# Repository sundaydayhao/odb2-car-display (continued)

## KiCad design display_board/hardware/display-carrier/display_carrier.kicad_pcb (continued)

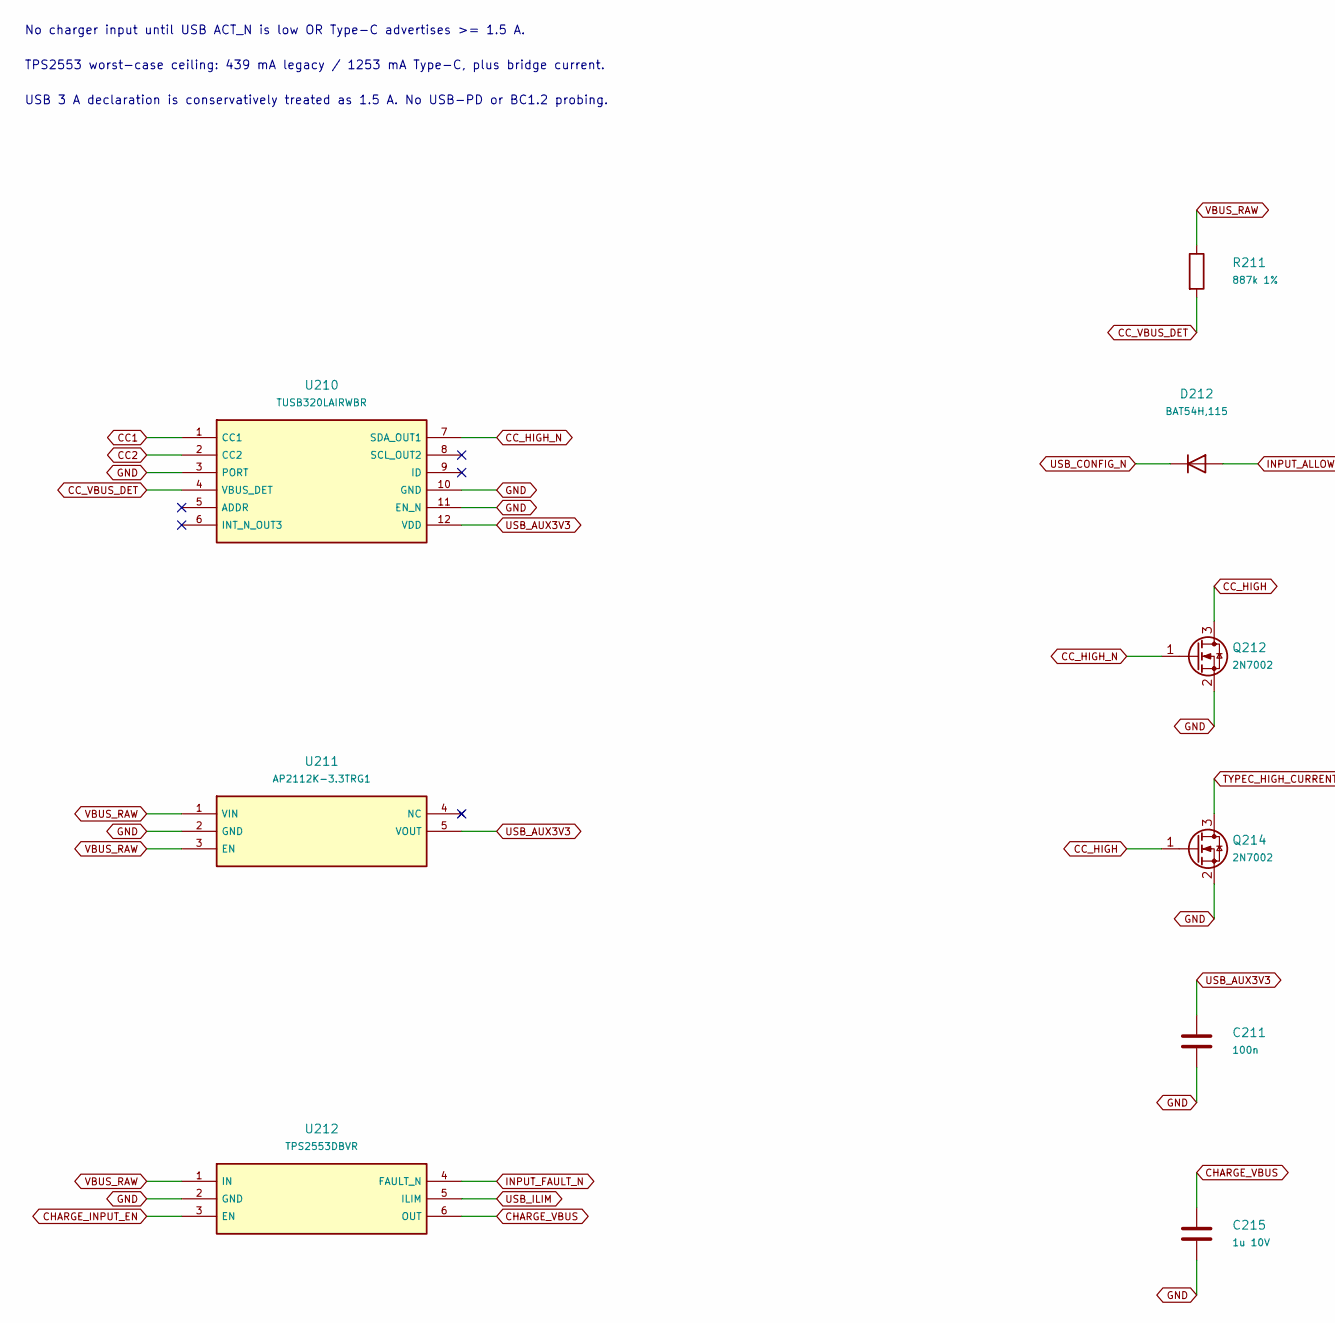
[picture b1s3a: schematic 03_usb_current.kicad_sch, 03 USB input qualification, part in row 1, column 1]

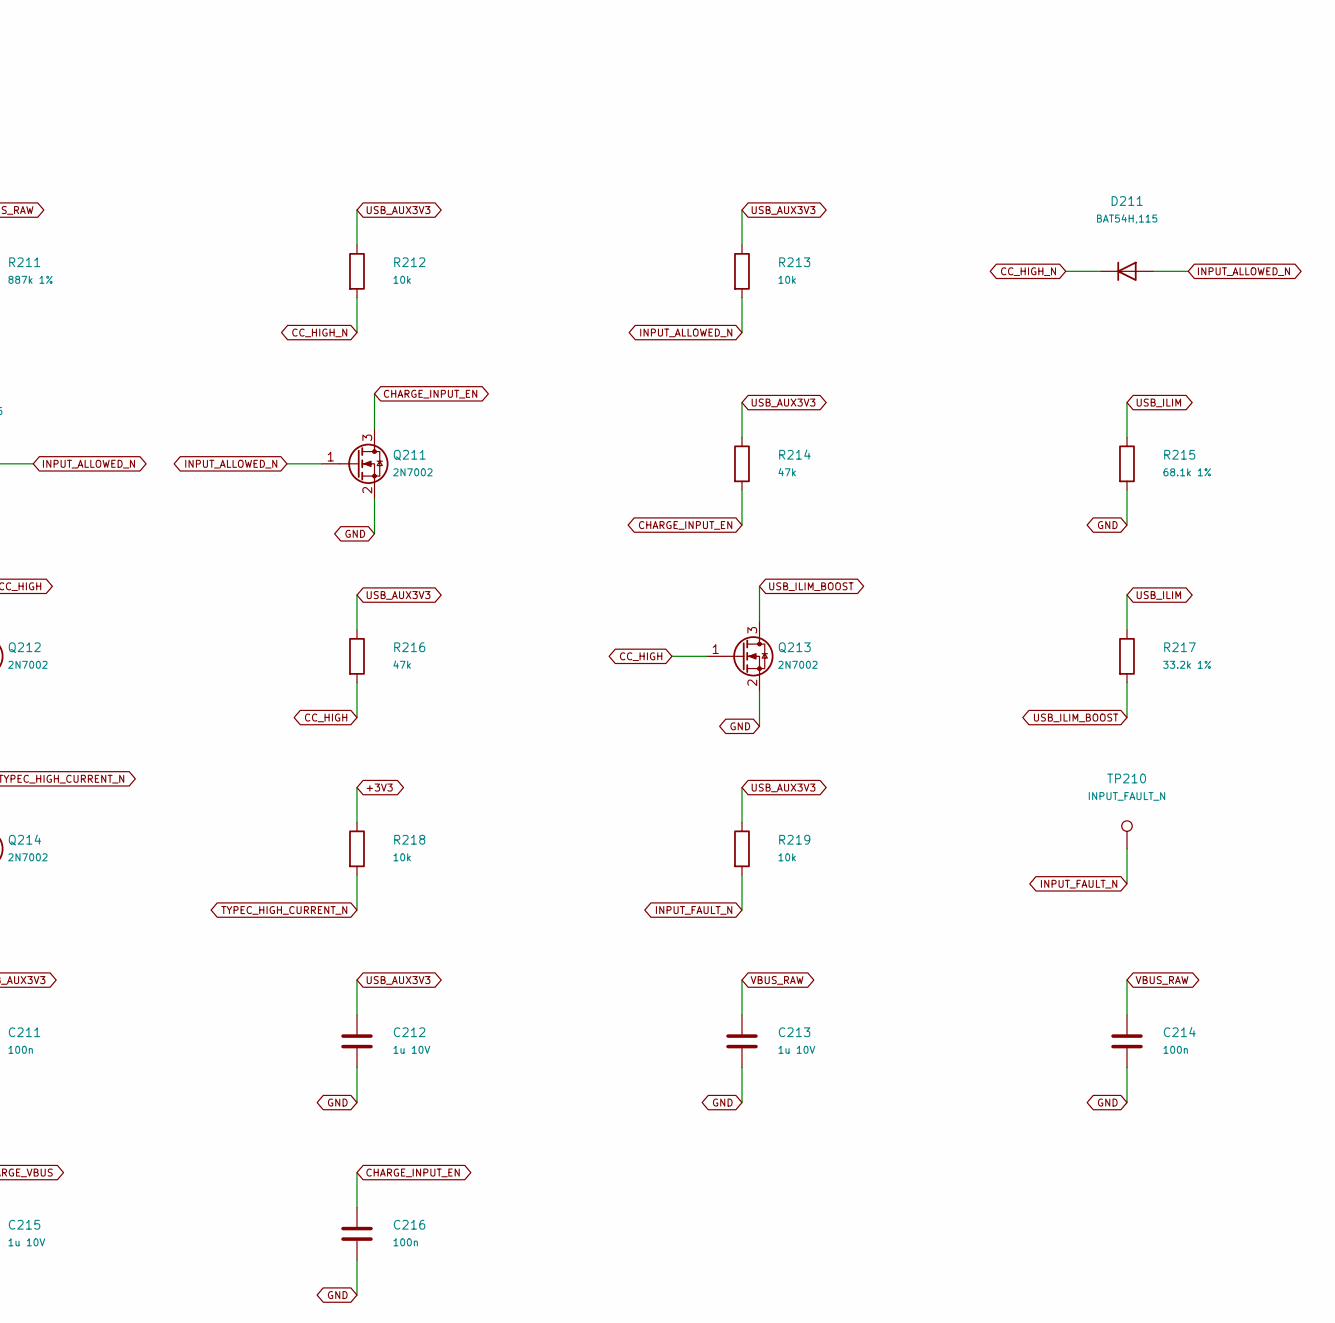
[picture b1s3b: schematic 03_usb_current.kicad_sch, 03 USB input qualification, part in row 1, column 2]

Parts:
C211, C214, C216: 100n; C_0402_1005Metric
C212, C213, C215: 1u 10V; C_0603_1608Metric
D211, D212: BAT54H,115; BAT54H_SOD123F
Q211, Q212, Q213, Q214: 2N7002; SOT-23
R211: 887k 1%; R_0603_1608Metric
R212, R213, R218, R219: 10k; R_0402_1005Metric
R214, R216: 47k; R_0402_1005Metric
R215: 68.1k 1%; R_0603_1608Metric
R217: 33.2k 1%; R_0603_1608Metric
TP210: INPUT_FAULT_N; TestPoint_Pad_D1.5mm
U210: TUSB320LAIRWBR; TUSB320_RWB12
U211: AP2112K-3.3TRG1; SOT-23-5
U212: TPS2553DBVR; SOT-23-6

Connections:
+3V3: R218.1; also elsewhere on the board
CC1: U210.1 (CC1); also elsewhere on the board
CC2: U210.2 (CC2); also elsewhere on the board
CC_HIGH: Q212.3 (D), Q213.1 (G), Q214.1 (G), R216.2
CC_HIGH_N: D211.1 (K), Q212.1 (G), R212.2, U210.7 (SDA_OUT1)
CC_VBUS_DET: R211.2, U210.4 (VBUS_DET)
CHARGE_INPUT_EN: C216.1, Q211.3 (D), R214.2, U212.3 (EN)
CHARGE_VBUS: C215.1, U212.6 (OUT); also elsewhere on the board
GND: C211.2, C212.2, C213.2, C214.2, C215.2, C216.2, Q211.2 (S), Q212.2 (S), Q213.2 (S), Q214.2 (S), R215.2, U210.3 (PORT), U210.10 (GND), U210.11 (EN_N), U211.2 (GND), U212.2 (GND); also elsewhere on the board
INPUT_ALLOWED_N: D211.2 (A), D212.2 (A), Q211.1 (G), R213.2
INPUT_FAULT_N: R219.2, TP210.1, U212.4 (FAULT_N)
TYPEC_HIGH_CURRENT_N: Q214.3 (D), R218.2; also elsewhere on the board
USB_AUX3V3: C211.1, C212.1, R212.1, R213.1, R214.1, R216.1, R219.1, U210.12 (VDD), U211.5 (VOUT); also elsewhere on the board
USB_CONFIG_N: D212.1 (K); also elsewhere on the board
USB_ILIM: R215.1, R217.1, U212.5 (ILIM)
USB_ILIM_BOOST: Q213.3 (D), R217.2
VBUS_RAW: C213.1, C214.1, R211.1, U211.1 (VIN), U211.3 (EN), U212.1 (IN); also elsewhere on the board

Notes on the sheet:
No charger input until USB ACT_N is low OR Type-C advertises >= 1.5 A.
TPS2553 worst-case ceiling: 439 mA legacy / 1253 mA Type-C, plus bridge current.
USB 3 A declaration is conservatively treated as 1.5 A. No USB-PD or BC1.2 probing.

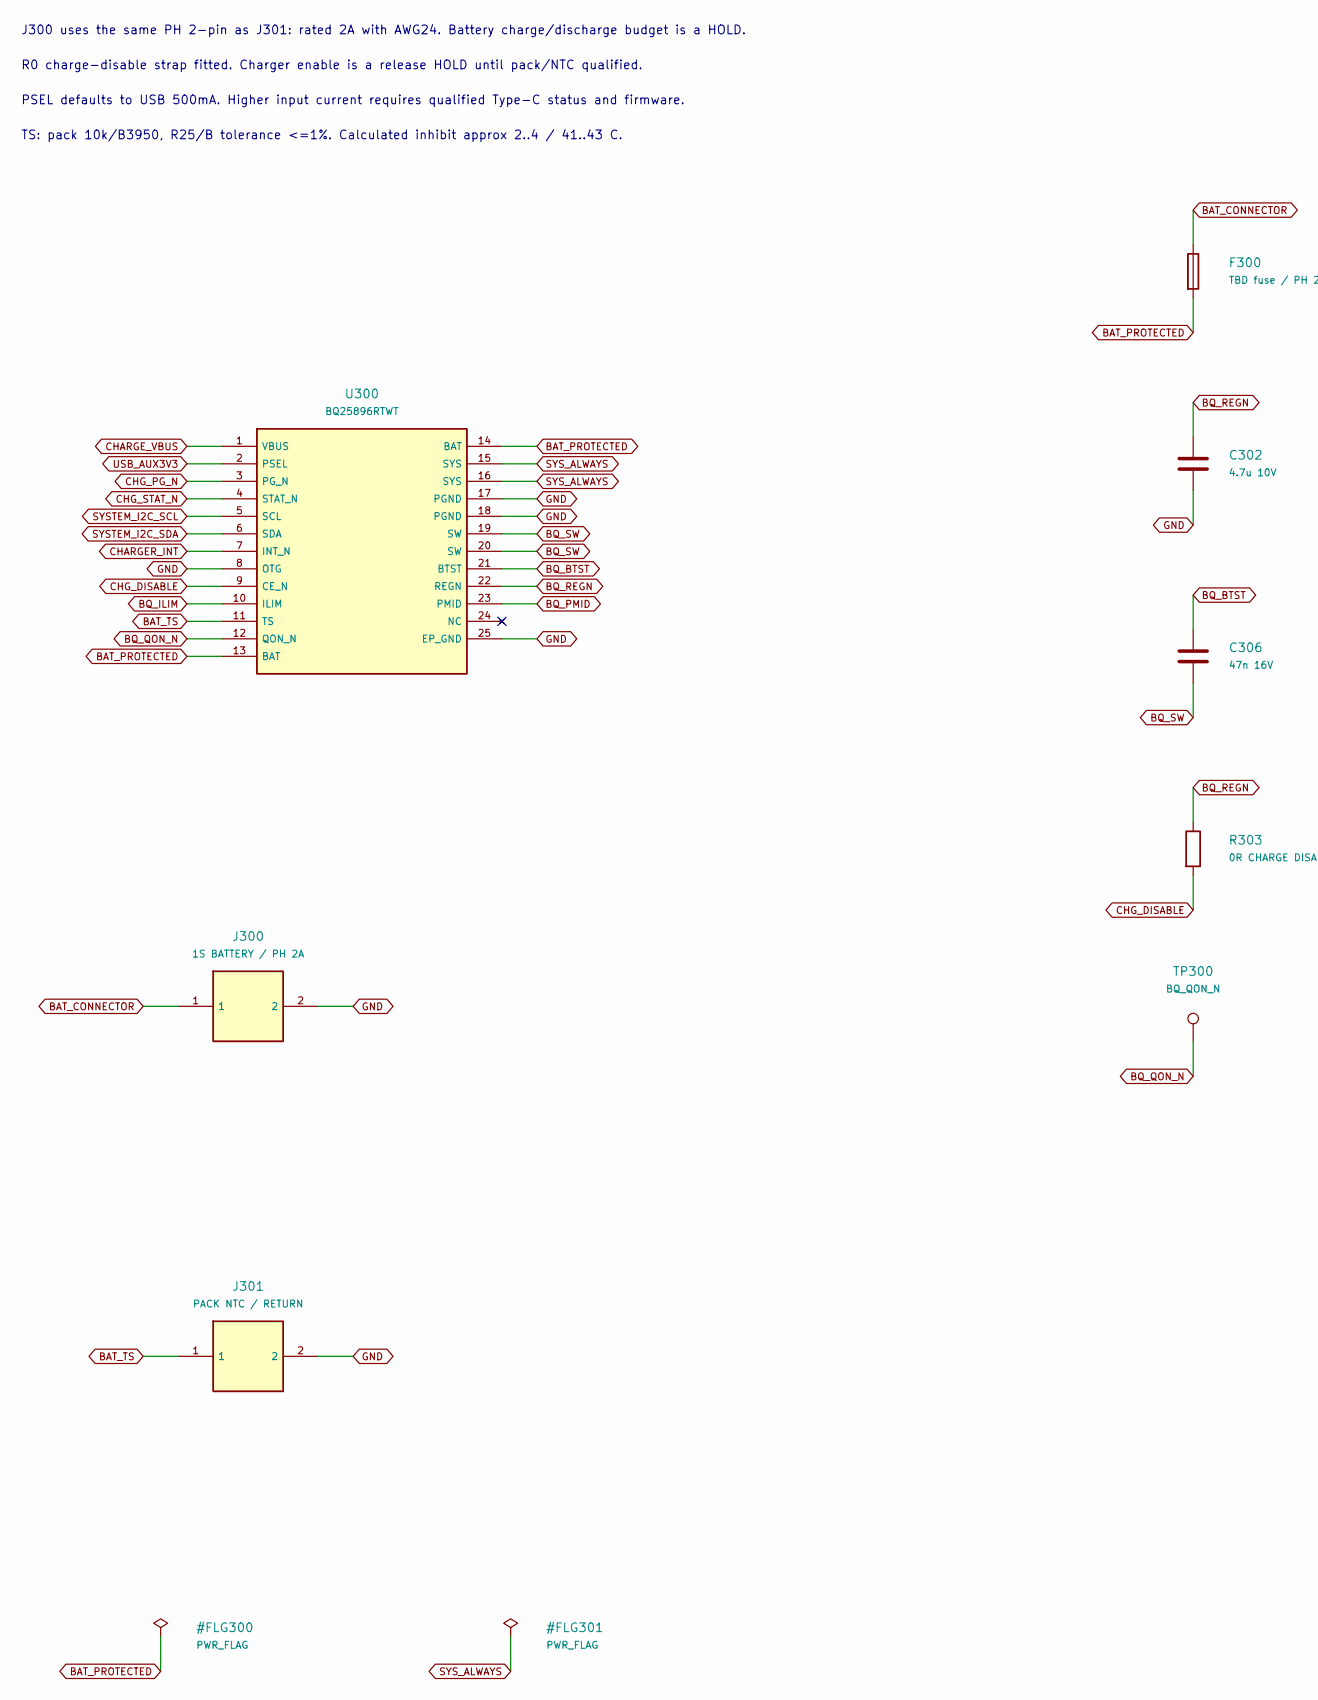
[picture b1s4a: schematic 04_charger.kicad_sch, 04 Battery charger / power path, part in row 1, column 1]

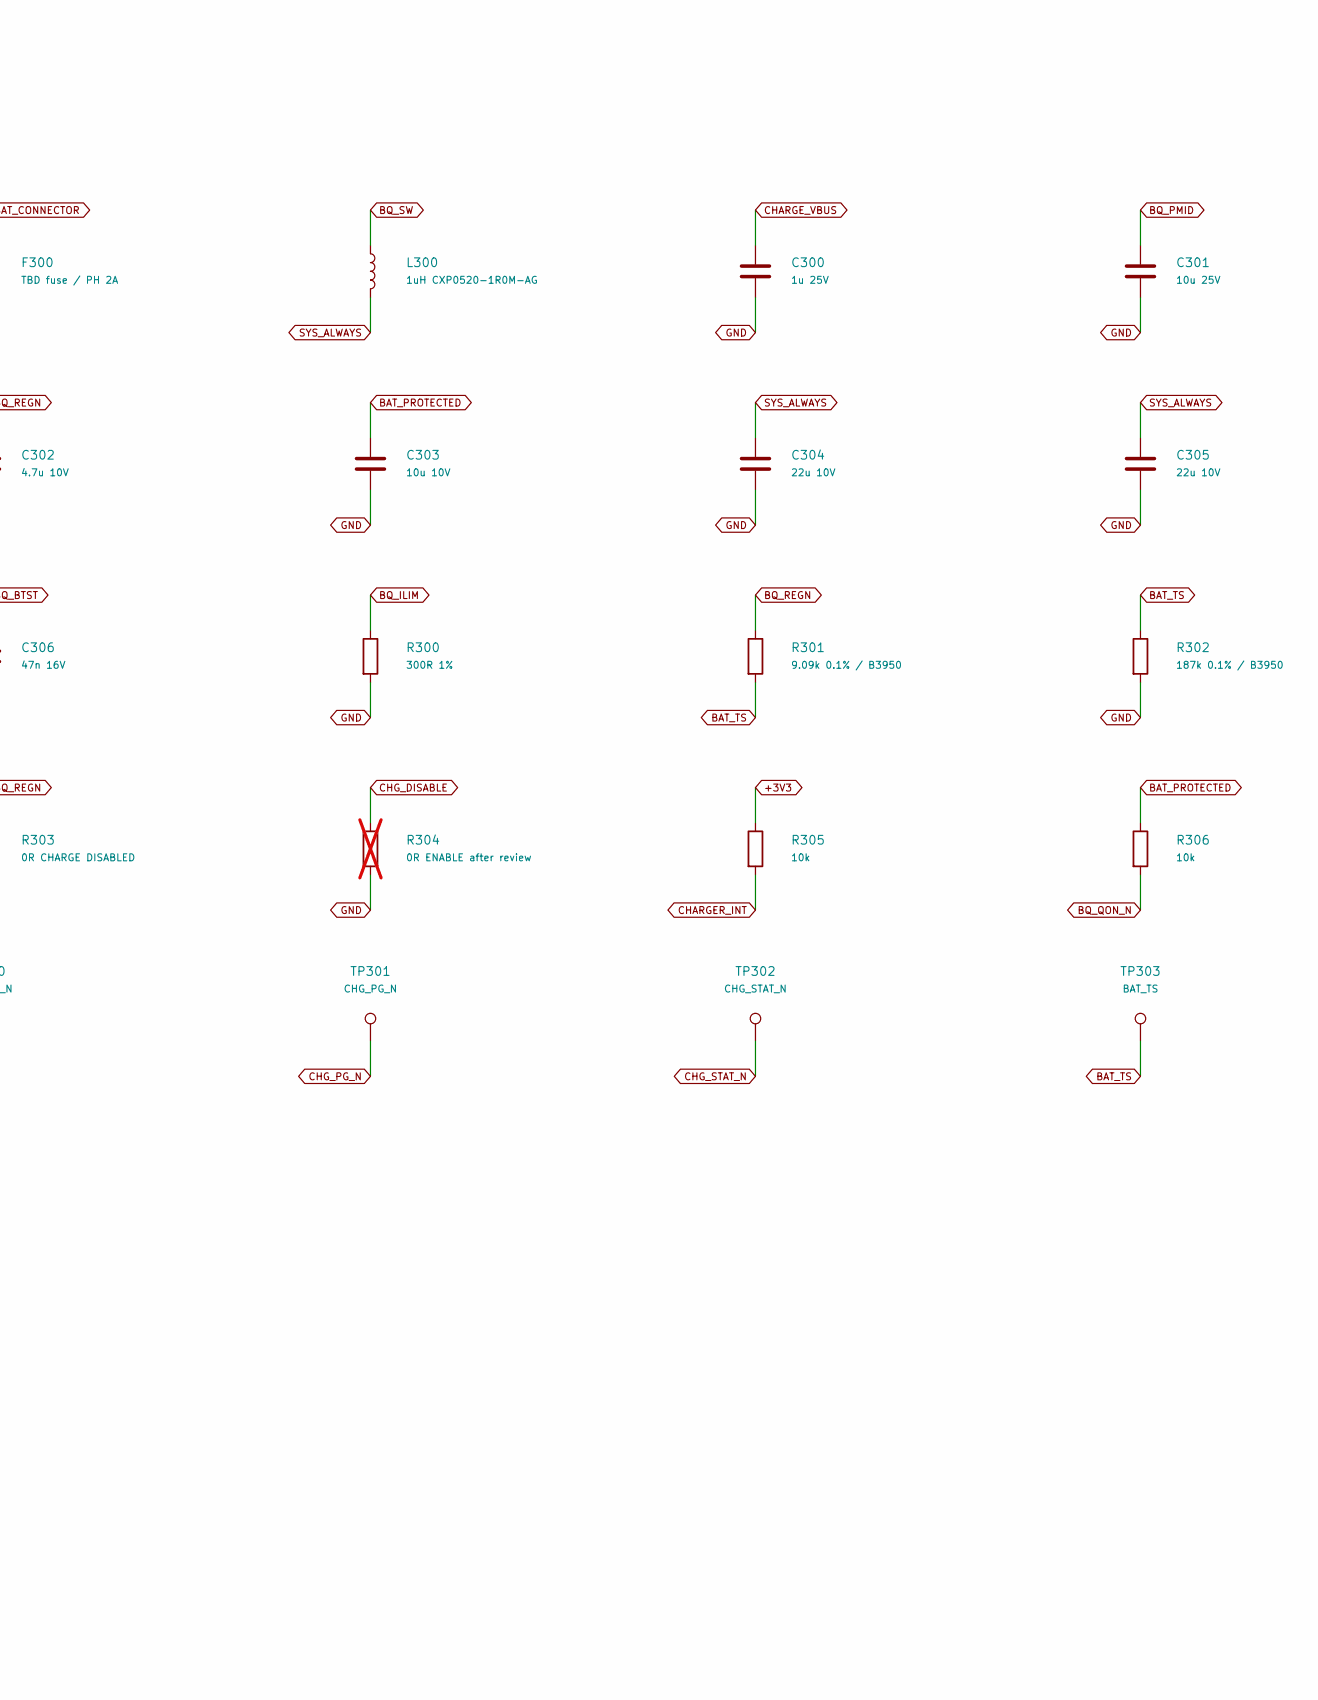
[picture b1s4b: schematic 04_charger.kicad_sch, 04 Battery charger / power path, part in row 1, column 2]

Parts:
C300: 1u 25V; C_0603_1608Metric
C301: 10u 25V; C_1206_3216Metric
C302: 4.7u 10V; C_0603_1608Metric
C303: 10u 10V; C_0805_2012Metric
C304, C305: 22u 10V; C_0805_2012Metric
C306: 47n 16V; C_0603_1608Metric
F300: TBD fuse / PH 2A; Fuse_1206_3216Metric
J300: 1S BATTERY / PH 2A; JST_PH_B2B-PH-K_1x02_P2.00mm_Vertical
J301: PACK NTC / RETURN; JST_PH_B2B-PH-K_1x02_P2.00mm_Vertical
L300: 1uH CXP0520-1R0M-AG; L_DMBJ_CXP0520
R300: 300R 1%; R_0603_1608Metric
R301: 9.09k 0.1% / B3950; R_0603_1608Metric
R302: 187k 0.1% / B3950; R_0603_1608Metric
R303: 0R CHARGE DISABLED; R_0603_1608Metric
R304: 0R ENABLE after review; R_0603_1608Metric; not fitted
R305, R306: 10k; R_0402_1005Metric
TP300: BQ_QON_N; TestPoint_Pad_D1.5mm
TP301: CHG_PG_N; TestPoint_Pad_D1.5mm
TP302: CHG_STAT_N; TestPoint_Pad_D1.5mm
TP303: BAT_TS; TestPoint_Pad_D1.5mm
U300: BQ25896RTWT; Texas_RTW_WQFN-24-1EP_4x4mm_P0.5mm_EP2.7x2.7mm

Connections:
+3V3: R305.1; also elsewhere on the board
BAT_CONNECTOR: F300.1, J300.1
BAT_PROTECTED: C303.1, F300.2, R306.1, U300.13 (BAT), U300.14 (BAT)
BAT_TS: J301.1, R301.2, R302.1, TP303.1, U300.11 (TS)
BQ_BTST: C306.1, U300.21 (BTST)
BQ_ILIM: R300.1, U300.10 (ILIM)
BQ_PMID: C301.1, U300.23 (PMID)
BQ_QON_N: R306.2, TP300.1, U300.12 (QON_N)
BQ_REGN: C302.1, R301.1, R303.1, U300.22 (REGN)
BQ_SW: C306.2, L300.1, U300.19 (SW), U300.20 (SW)
CHARGER_INT: R305.2, U300.7 (INT_N); also elsewhere on the board
CHARGE_VBUS: C300.1, U300.1 (VBUS); also elsewhere on the board
CHG_DISABLE: R303.2, R304.1, U300.9 (CE_N)
CHG_PG_N: TP301.1, U300.3 (PG_N)
CHG_STAT_N: TP302.1, U300.4 (STAT_N)
GND: C300.2, C301.2, C302.2, C303.2, C304.2, C305.2, J300.2, J301.2, R300.2, R302.2, R304.2, U300.8 (OTG), U300.17 (PGND), U300.18 (PGND), U300.25 (EP_GND); also elsewhere on the board
SYSTEM_I2C_SCL: U300.5 (SCL); also elsewhere on the board
SYSTEM_I2C_SDA: U300.6 (SDA); also elsewhere on the board
SYS_ALWAYS: C304.1, C305.1, L300.2, U300.15 (SYS), U300.16 (SYS); also elsewhere on the board
USB_AUX3V3: U300.2 (PSEL); also elsewhere on the board

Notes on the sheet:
J300 uses the same PH 2-pin as J301: rated 2A with AWG24. Battery charge/discharge budget is a HOLD.
R0 charge-disable strap fitted. Charger enable is a release HOLD until pack/NTC qualified.
PSEL defaults to USB 500mA. Higher input current requires qualified Type-C status and firmware.
TS: pack 10k/B3950, R25/B tolerance <=1%. Calculated inhibit approx 2..4 / 41..43 C.

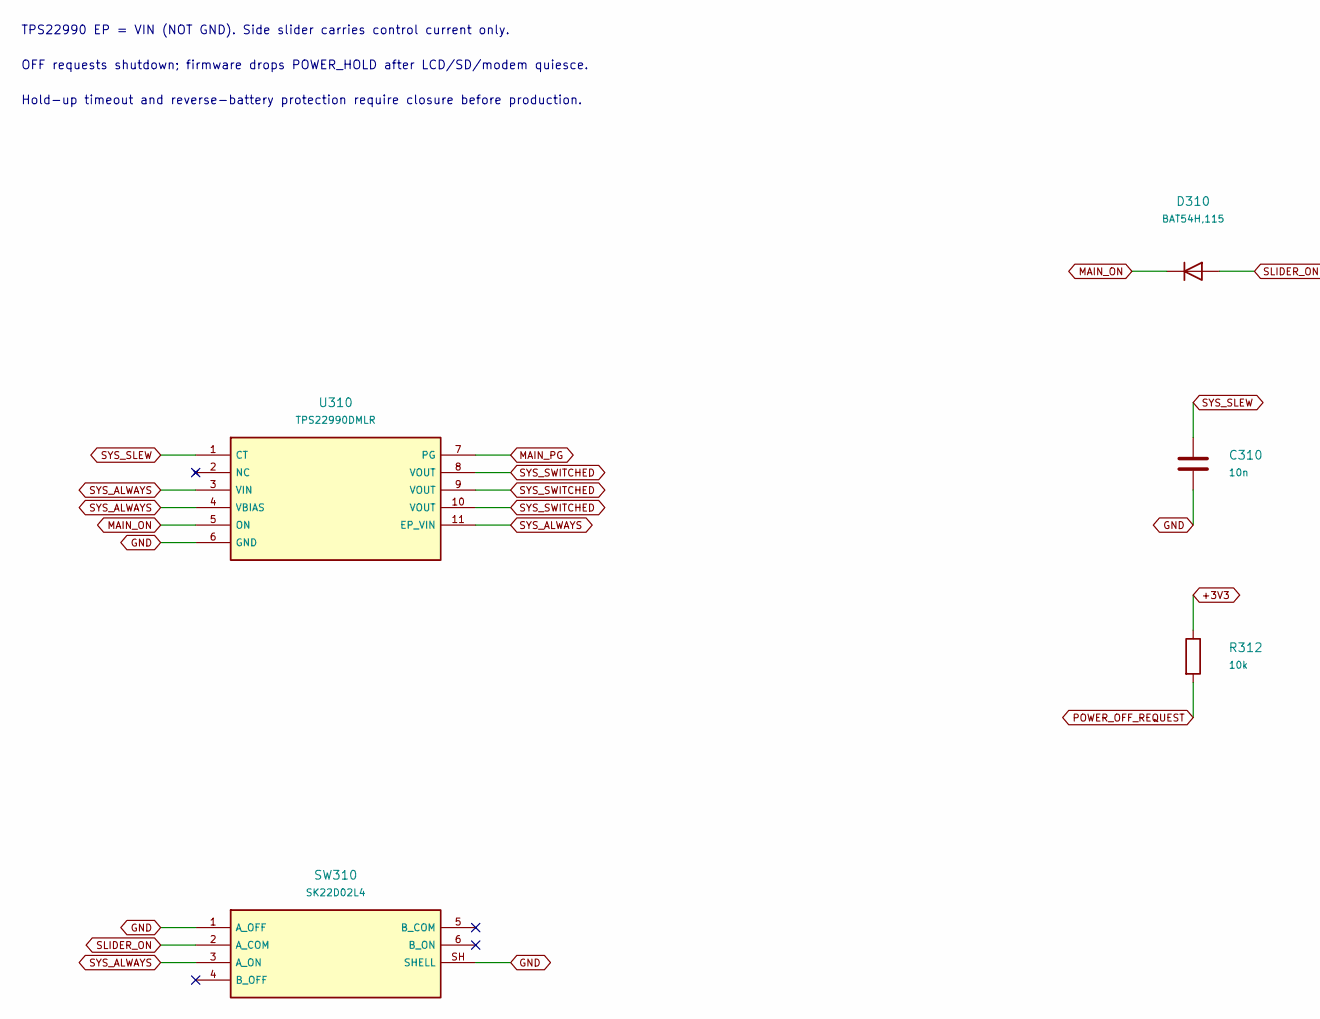
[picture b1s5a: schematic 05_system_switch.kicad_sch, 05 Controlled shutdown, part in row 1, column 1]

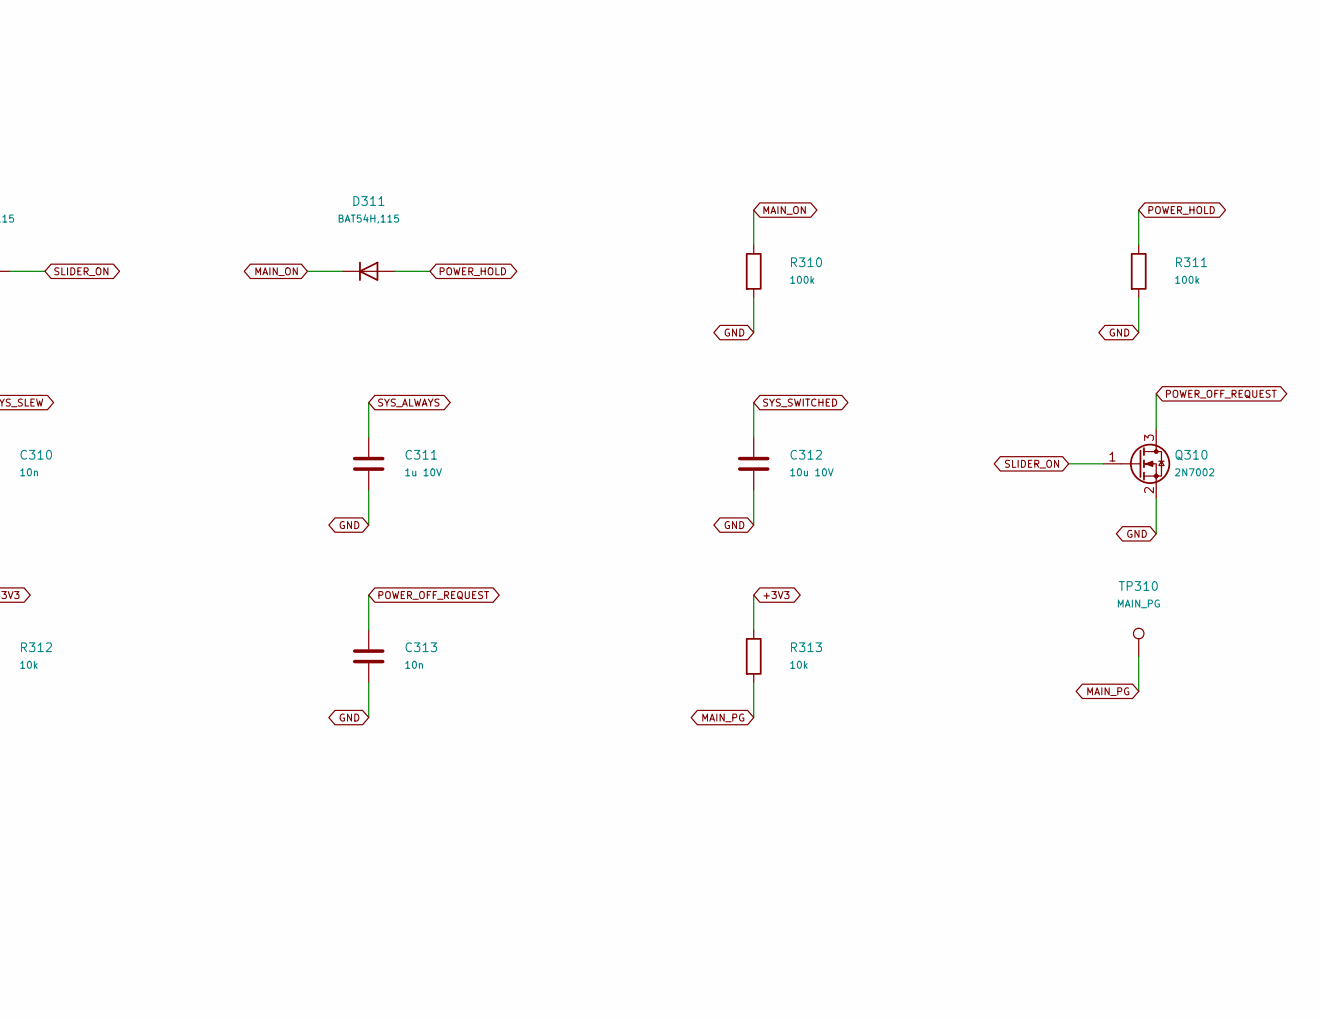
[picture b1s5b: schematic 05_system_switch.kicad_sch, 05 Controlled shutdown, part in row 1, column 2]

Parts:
C310, C313: 10n; C_0603_1608Metric
C311: 1u 10V; C_0603_1608Metric
C312: 10u 10V; C_0805_2012Metric
D310, D311: BAT54H,115; BAT54H_SOD123F
Q310: 2N7002; SOT-23
R310, R311: 100k; R_0402_1005Metric
R312, R313: 10k; R_0402_1005Metric
SW310: SK22D02L4; SK22D02L4_SideSlide
TP310: MAIN_PG; TestPoint_Pad_D1.5mm
U310: TPS22990DMLR; TPS22990_DML10

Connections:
+3V3: R312.1, R313.1; also elsewhere on the board
GND: C310.2, C311.2, C312.2, C313.2, Q310.2 (S), R310.2, R311.2, SW310.1 (A_OFF), SW310.SH (SHELL), U310.6 (GND); also elsewhere on the board
MAIN_ON: D310.1 (K), D311.1 (K), R310.1, U310.5 (ON)
MAIN_PG: R313.2, TP310.1, U310.7 (PG)
POWER_HOLD: D311.2 (A), R311.1; also elsewhere on the board
POWER_OFF_REQUEST: C313.1, Q310.3 (D), R312.2; also elsewhere on the board
SLIDER_ON: D310.2 (A), Q310.1 (G), SW310.2 (A_COM)
SYS_ALWAYS: C311.1, SW310.3 (A_ON), U310.3 (VIN), U310.4 (VBIAS), U310.11 (EP_VIN); also elsewhere on the board
SYS_SLEW: C310.1, U310.1 (CT)
SYS_SWITCHED: C312.1, U310.8 (VOUT), U310.9 (VOUT), U310.10 (VOUT); also elsewhere on the board

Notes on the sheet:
TPS22990 EP = VIN (NOT GND). Side slider carries control current only.
OFF requests shutdown; firmware drops POWER_HOLD after LCD/SD/modem quiesce.
Hold-up timeout and reverse-battery protection require closure before production.

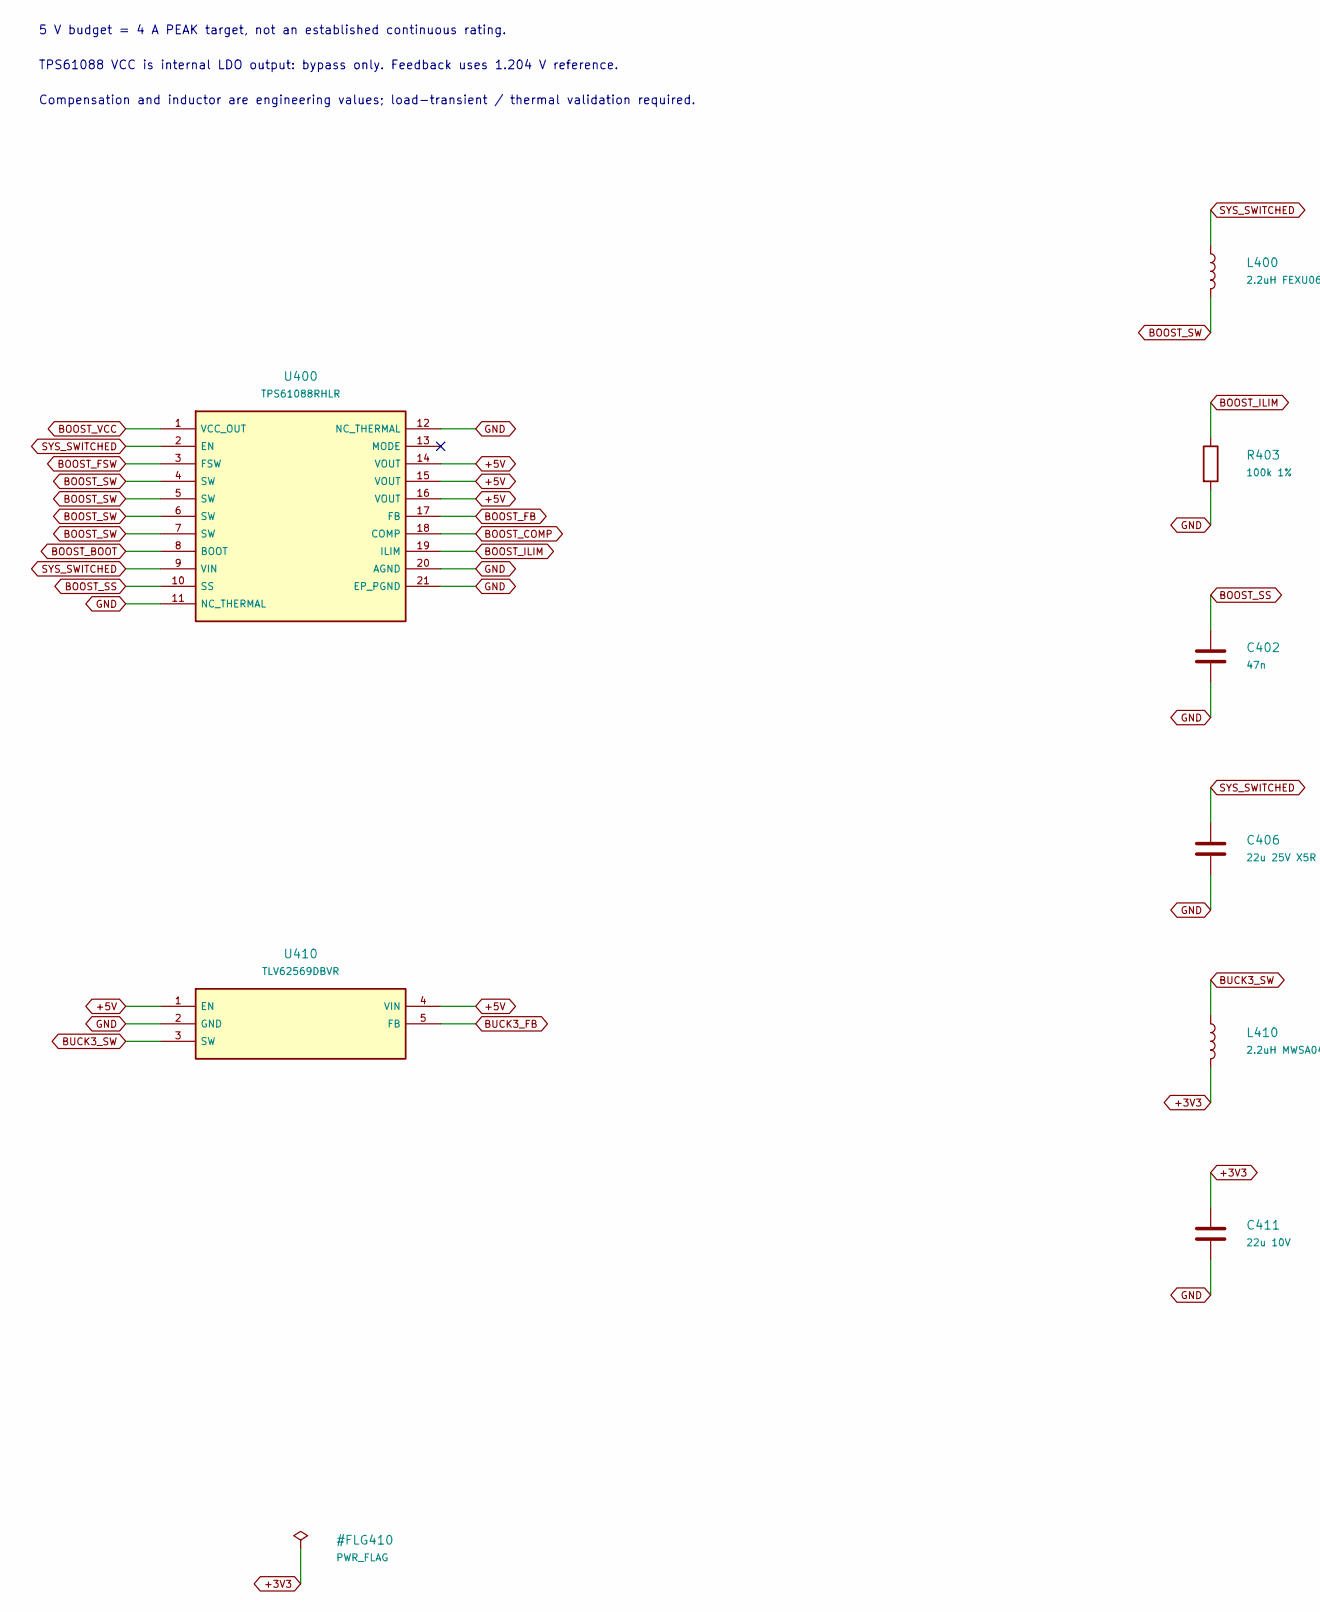
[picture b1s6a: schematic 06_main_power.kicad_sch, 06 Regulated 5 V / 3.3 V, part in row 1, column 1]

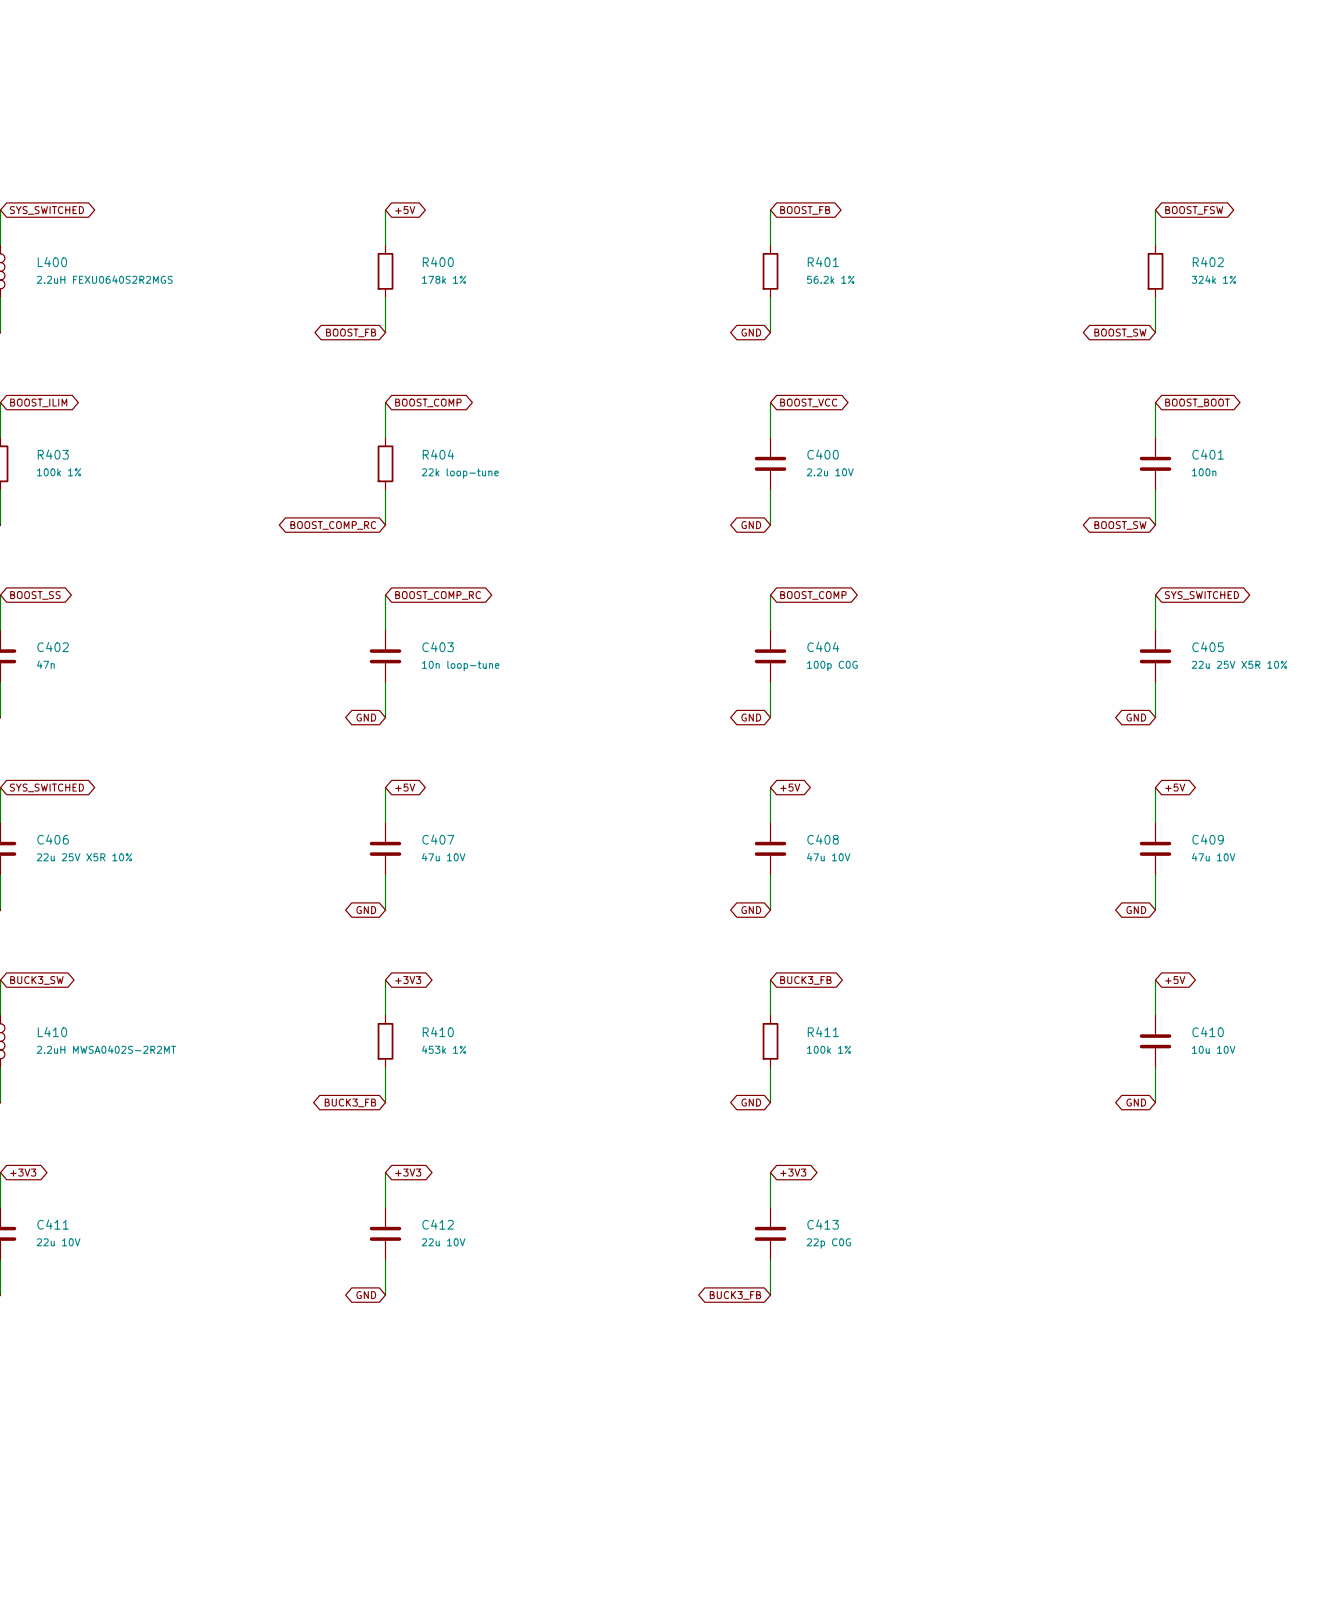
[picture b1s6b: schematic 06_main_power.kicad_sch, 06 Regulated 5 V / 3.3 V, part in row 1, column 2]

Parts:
C400: 2.2u 10V; C_0603_1608Metric
C401: 100n; C_0402_1005Metric
C402: 47n; C_0603_1608Metric
C403: 10n loop-tune; C_0603_1608Metric
C404: 100p C0G; C_0402_1005Metric
C405, C406: 22u 25V X5R 10%; C_1206_3216Metric
C407, C408, C409: 47u 10V; C_1210_3225Metric
C410: 10u 10V; C_0805_2012Metric
C411, C412: 22u 10V; C_0805_2012Metric
C413: 22p C0G; C_0402_1005Metric
L400: 2.2uH FEXU0640S2R2MGS; L_Cjiang_FEXU0640_6.2x6.0mm
L410: 2.2uH MWSA0402S-2R2MT; L_Sunlord_MWSA0402S
R400: 178k 1%; R_0603_1608Metric
R401: 56.2k 1%; R_0603_1608Metric
R402: 324k 1%; R_0603_1608Metric
R403, R411: 100k 1%; R_0402_1005Metric
R404: 22k loop-tune; R_0402_1005Metric
R410: 453k 1%; R_0603_1608Metric
U400: TPS61088RHLR; Texas_VQFN-RHL-20
U410: TLV62569DBVR; SOT-23-5

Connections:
+3V3: C411.1, C412.1, C413.1, L410.2, R410.1; also elsewhere on the board
+5V: C407.1, C408.1, C409.1, C410.1, R400.1, U400.14 (VOUT), U400.15 (VOUT), U400.16 (VOUT), U410.1 (EN), U410.4 (VIN); also elsewhere on the board
BOOST_BOOT: C401.1, U400.8 (BOOT)
BOOST_COMP: C404.1, R404.1, U400.18 (COMP)
BOOST_COMP_RC: C403.1, R404.2
BOOST_FB: R400.2, R401.1, U400.17 (FB)
BOOST_FSW: R402.1, U400.3 (FSW)
BOOST_ILIM: R403.1, U400.19 (ILIM)
BOOST_SS: C402.1, U400.10 (SS)
BOOST_SW: C401.2, L400.2, R402.2, U400.4 (SW), U400.5 (SW), U400.6 (SW), U400.7 (SW)
BOOST_VCC: C400.1, U400.1 (VCC_OUT)
BUCK3_FB: C413.2, R410.2, R411.1, U410.5 (FB)
BUCK3_SW: L410.1, U410.3 (SW)
GND: C400.2, C402.2, C403.2, C404.2, C405.2, C406.2, C407.2, C408.2, C409.2, C410.2, C411.2, C412.2, R401.2, R403.2, R411.2, U400.11 (NC_THERMAL), U400.12 (NC_THERMAL), U400.20 (AGND), U400.21 (EP_PGND), U410.2 (GND); also elsewhere on the board
SYS_SWITCHED: C405.1, C406.1, L400.1, U400.2 (EN), U400.9 (VIN); also elsewhere on the board

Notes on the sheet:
5 V budget = 4 A PEAK target, not an established continuous rating.
TPS61088 VCC is internal LDO output: bypass only. Feedback uses 1.204 V reference.
Compensation and inductor are engineering values; load-transient / thermal validation required.
